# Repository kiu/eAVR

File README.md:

# eAVR
eAVR replaces the standard 6P (2x03) pinheader or 6P (2x03) IDC socket for AVR device programming and debugging with an edge connector.

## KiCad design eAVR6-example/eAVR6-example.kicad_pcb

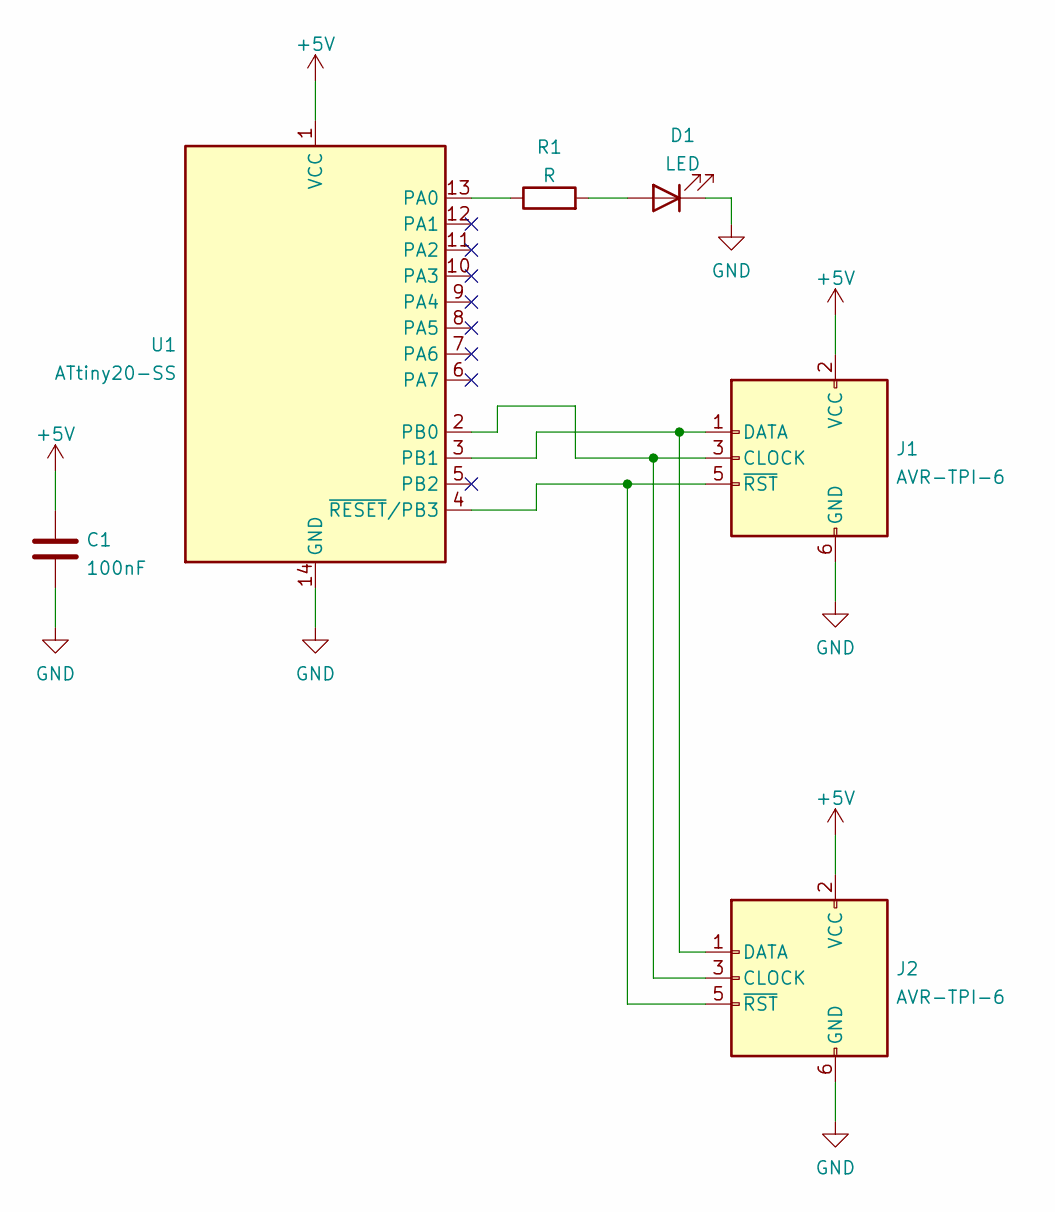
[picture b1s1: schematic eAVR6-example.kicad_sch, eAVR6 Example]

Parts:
C1: 100nF; C_0805_2012Metric
D1: LED; LED_0805_2012Metric
J1, J2: AVR-TPI-6; eAVR6
R1: R; R_0805_2012Metric
U1: ATtiny20-SS; SOIC-14_3.9x8.7mm_P1.27mm

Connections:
+5V: C1.1, J1.2 (VCC), J2.2 (VCC), U1.1 (VCC)
GND: C1.2, D1.1 (K), J1.6 (GND), J2.6 (GND), U1.14 (GND)
unnamed: D1.2 (A), R1.2
unnamed: J1.1 (DATA), J2.1 (DATA), U1.3 (PB1)
unnamed: J1.3 (CLOCK), J2.3 (CLOCK), U1.2 (PB0)
unnamed: J1.5 (~RST), J2.5 (~RST), U1.4 (~RESET/PB3)
unnamed: R1.1, U1.13 (PA0)

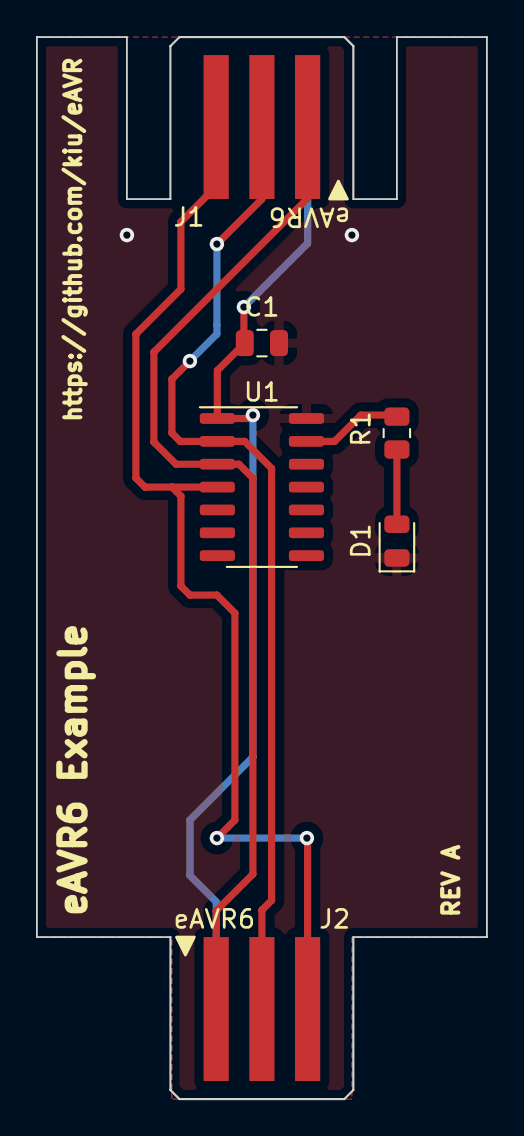
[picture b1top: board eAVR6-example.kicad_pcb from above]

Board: 2 copper layers, 25.0 x 59.0 mm, 6 parts (0 on the bottom side), 7 nets.

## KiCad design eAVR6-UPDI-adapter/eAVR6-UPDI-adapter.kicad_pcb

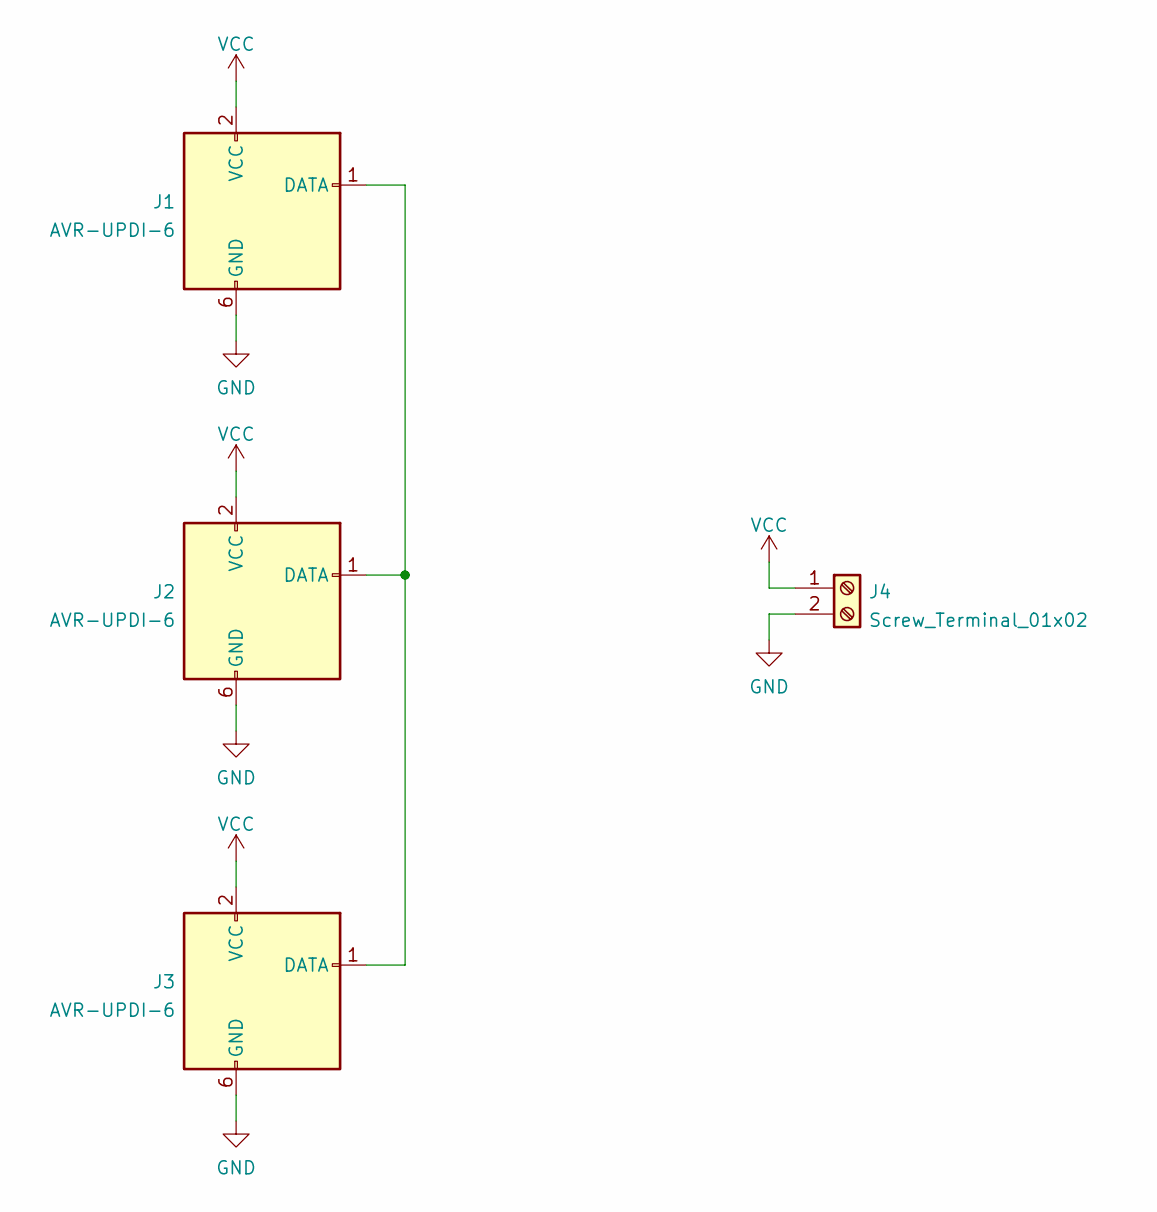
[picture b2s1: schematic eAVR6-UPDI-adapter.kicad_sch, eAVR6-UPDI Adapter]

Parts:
J1: AVR-UPDI-6; IDC-Header_2x03_P2.54mm_Vertical
J2, J3: AVR-UPDI-6; eAVR6-UPDI-EdgeSocket_2x03_P2.54mm_Vertical
J4: Screw_Terminal_01x02; TerminalBlock_bornier-2_P5.08mm

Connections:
GND: J1.6 (GND), J2.6 (GND), J3.6 (GND), J4.2
unnamed: J1.1 (DATA), J2.1 (DATA), J3.1 (DATA)
VCC: J1.2 (VCC), J2.2 (VCC), J3.2 (VCC), J4.1

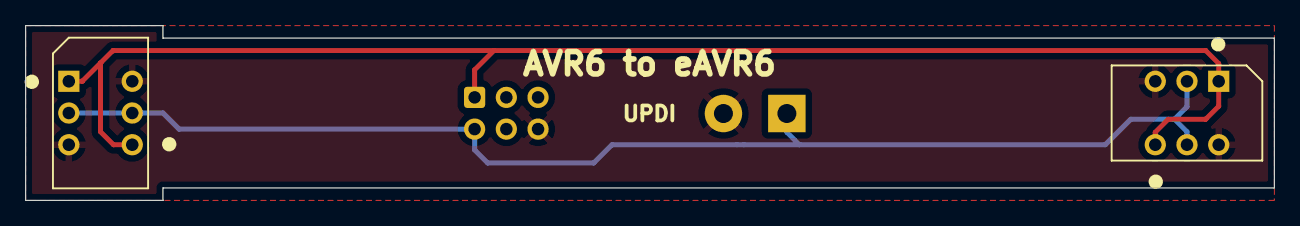
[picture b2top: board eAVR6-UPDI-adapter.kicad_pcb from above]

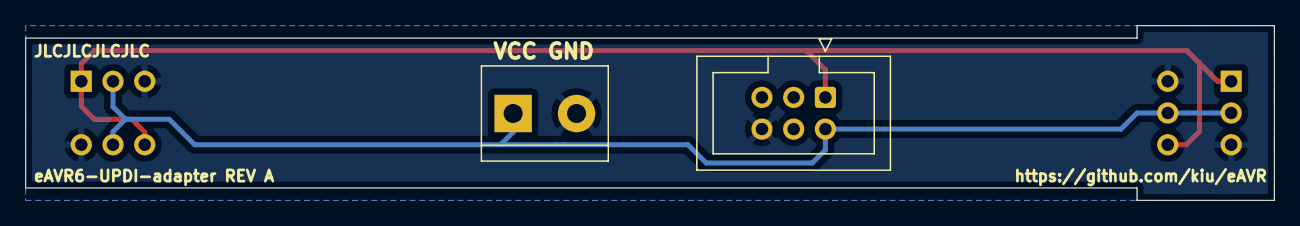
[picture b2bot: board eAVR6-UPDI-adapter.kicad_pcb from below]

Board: 2 copper layers, 100.0 x 14.0 mm, 4 parts (2 on the bottom side), 3 nets.

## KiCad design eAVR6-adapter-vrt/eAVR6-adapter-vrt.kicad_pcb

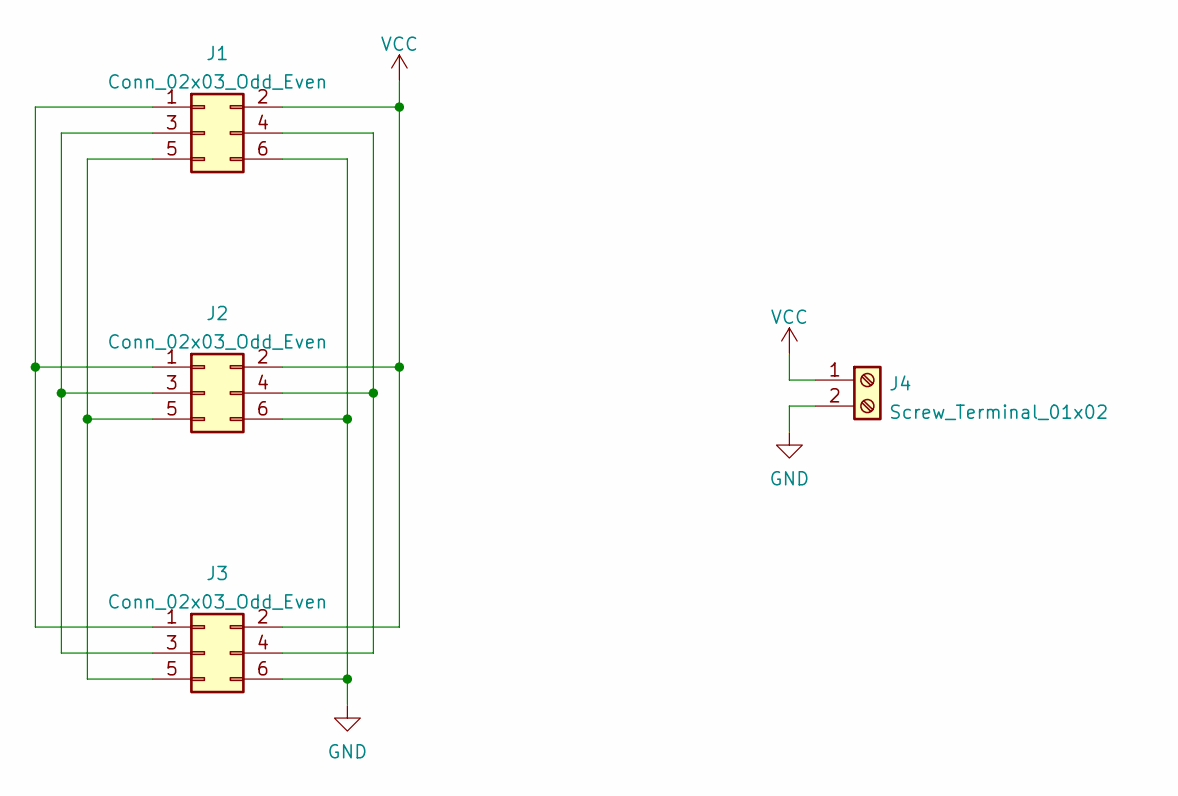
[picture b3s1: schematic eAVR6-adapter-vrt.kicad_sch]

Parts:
J1, J3: Conn_02x03_Odd_Even; eAVR6-EdgeSocket_2x03_P2.54mm_Vertical
J2: Conn_02x03_Odd_Even; IDC-Header_2x03_P2.54mm_Vertical
J4: Screw_Terminal_01x02; TerminalBlock_bornier-2_P5.08mm

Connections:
GND: J1.6, J2.6, J3.6, J4.2
unnamed: J1.1, J2.1, J3.1
unnamed: J1.3, J2.3, J3.3
unnamed: J1.4, J2.4, J3.4
unnamed: J1.5, J2.5, J3.5
VCC: J1.2, J2.2, J3.2, J4.1

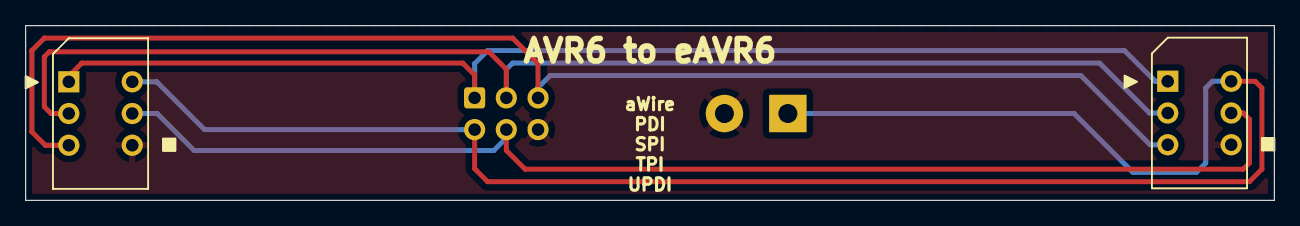
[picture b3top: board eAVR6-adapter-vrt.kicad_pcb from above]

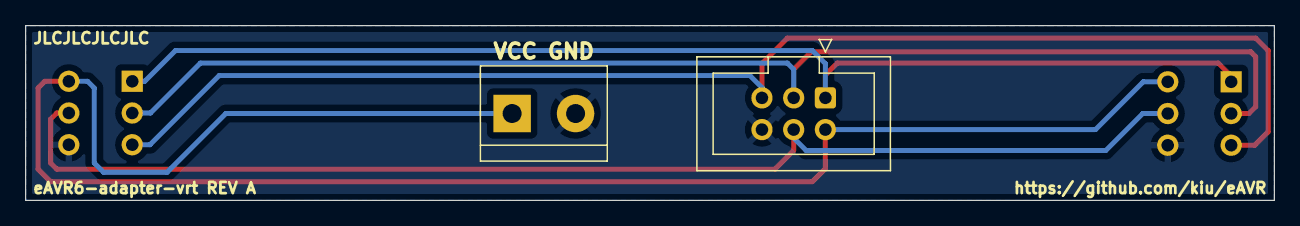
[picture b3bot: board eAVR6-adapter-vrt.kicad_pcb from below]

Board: 2 copper layers, 100.0 x 14.0 mm, 4 parts (2 on the bottom side), 6 nets.

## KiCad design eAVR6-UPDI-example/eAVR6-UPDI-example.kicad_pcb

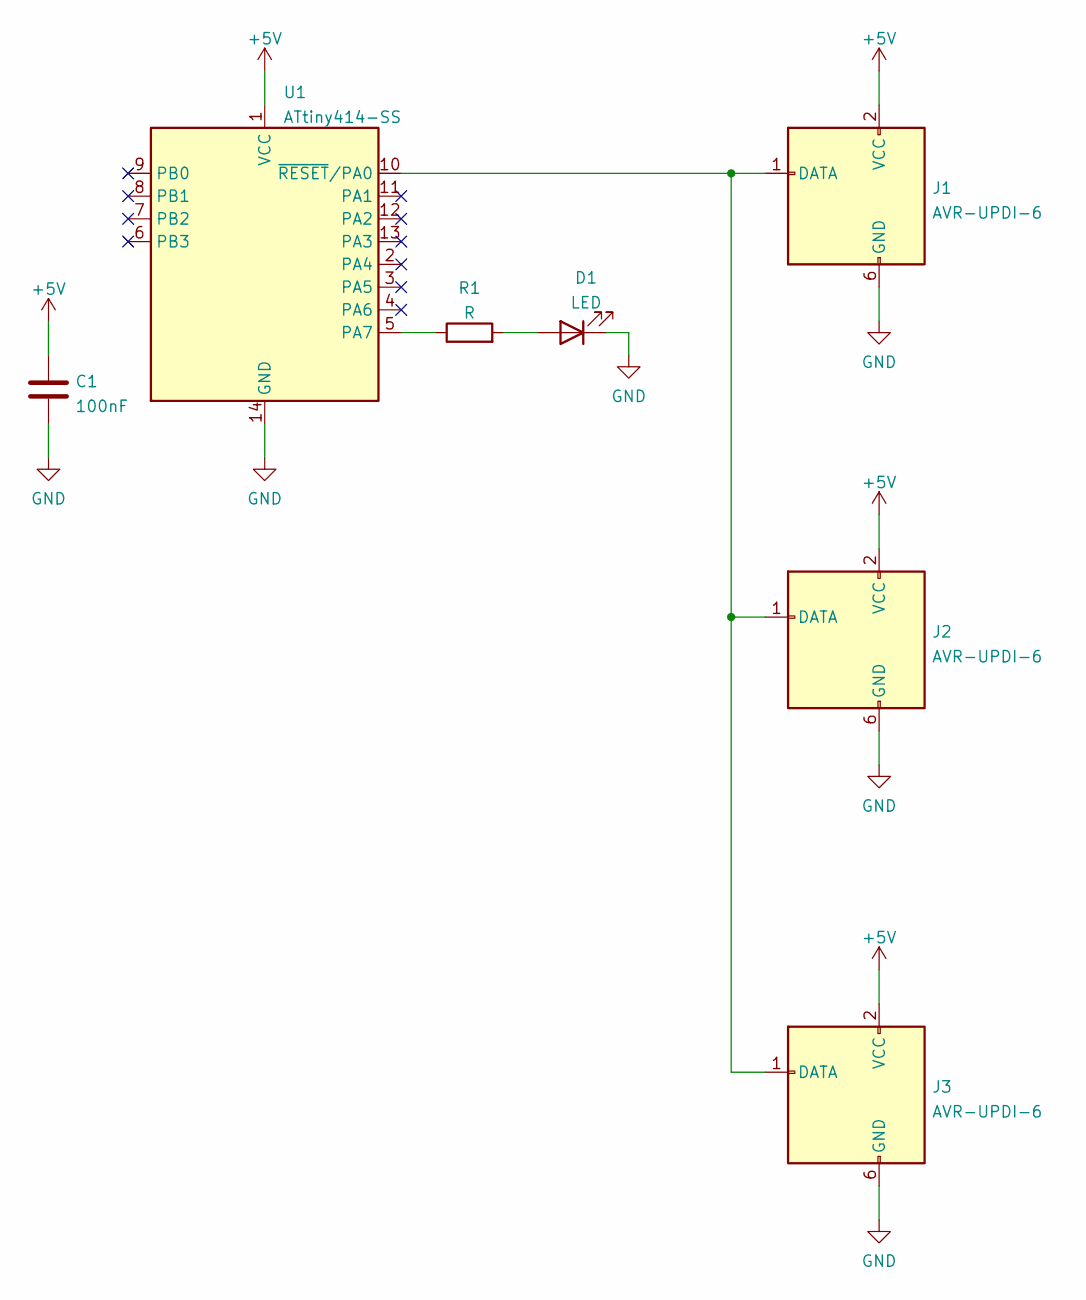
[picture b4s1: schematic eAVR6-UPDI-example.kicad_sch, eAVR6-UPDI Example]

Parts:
C1: 100nF; C_0805_2012Metric
D1: LED; LED_0805_2012Metric
J1: AVR-UPDI-6; eAVR6-UPDI-F
J2: AVR-UPDI-6; eAVR6-UPDI-FB
J3: AVR-UPDI-6; eAVR6-UPDI-B
R1: R; R_0805_2012Metric
U1: ATtiny414-SS; SOIC-14_3.9x8.7mm_P1.27mm

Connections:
+5V: C1.1, J1.2 (VCC), J2.2 (VCC), J3.2 (VCC), U1.1 (VCC)
GND: C1.2, D1.1 (K), J1.6 (GND), J2.6 (GND), J3.6 (GND), U1.14 (GND)
unnamed: D1.2 (A), R1.2
unnamed: J1.1 (DATA), J2.1 (DATA), J3.1 (DATA), U1.10 (~RESET/PA0)
unnamed: R1.1, U1.5 (PA7)

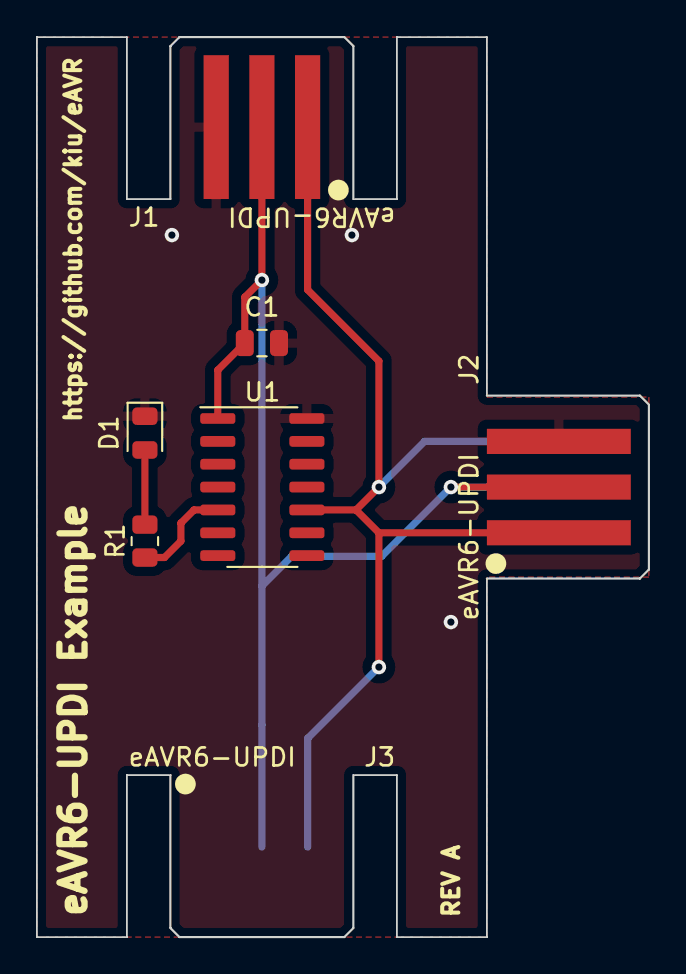
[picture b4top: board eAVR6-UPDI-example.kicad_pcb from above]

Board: 2 copper layers, 34.0 x 50.0 mm, 7 parts (0 on the bottom side), 5 nets.

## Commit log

2023-01-05 init
